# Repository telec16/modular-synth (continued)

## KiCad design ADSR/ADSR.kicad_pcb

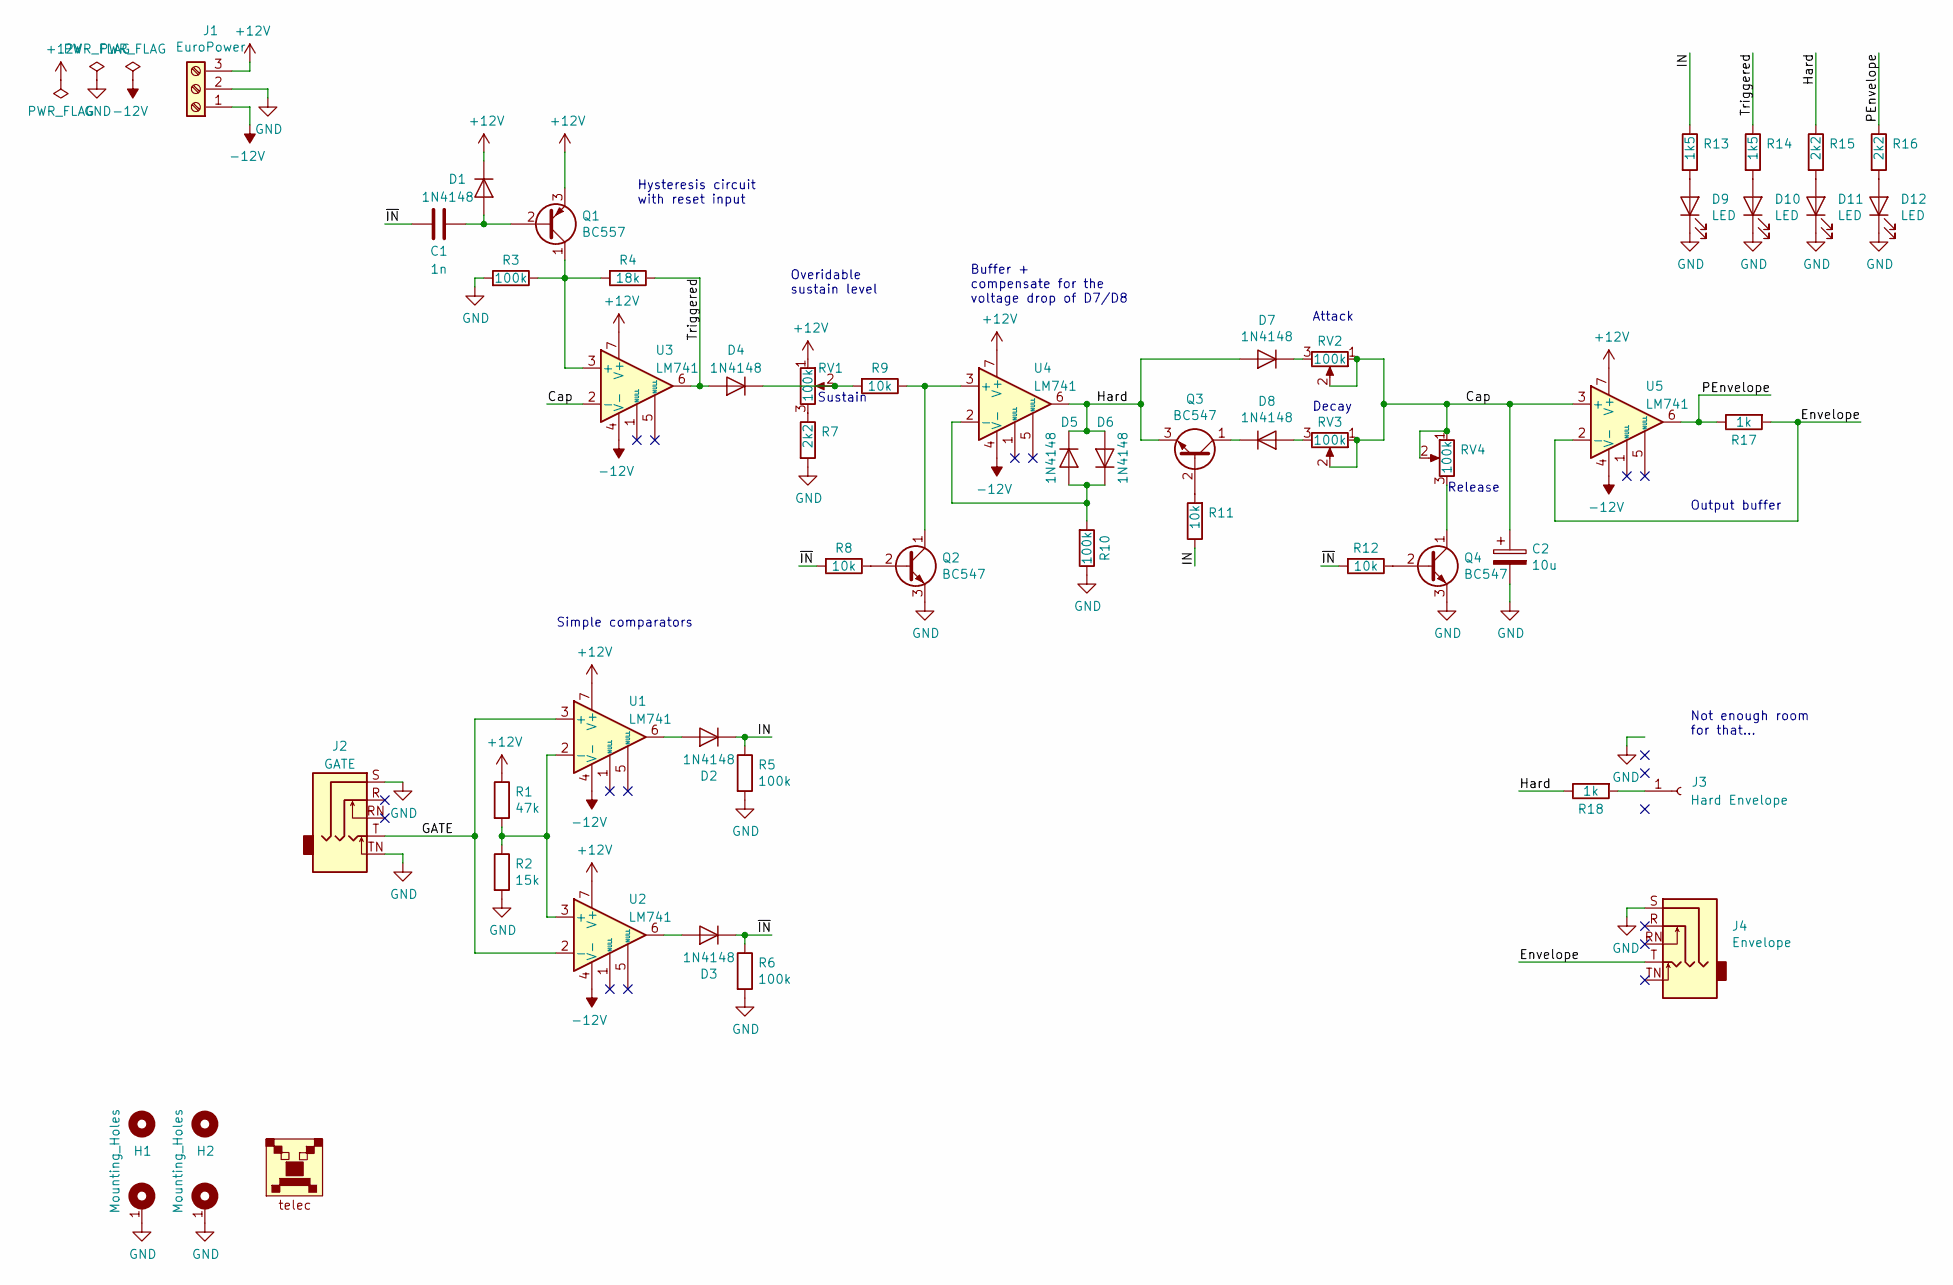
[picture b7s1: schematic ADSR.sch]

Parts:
C1: 1n; C_Disc_D7.0mm_W2.5mm_P5.00mm
C2: 10u; CP_Radial_D6.3mm_P2.50mm
D1, D2, D3, D4, D5, D6, D7, D8: 1N4148; D_DO-35_SOD27_P7.62mm_Horizontal
D9, D10, D11, D12: LED; LED_1206_3216Metric_ReverseMount_Hole1.8x2.4mm
H1, H2: Mounting_Holes; Kosmo_Panel_Dual_Mounting_Holes
J1: EuroPower
J2: GATE; Jack_Hole_Square
J3: Hard Envelope; PinSocket_1x01_P2.54mm_Vertical
J4: Envelope; Jack_Hole_Square
LOGO1: Logo_telec; telec-8
Q1: BC557; TO-92_Inline_Wide
Q2, Q3, Q4: BC547; TO-92_Inline_Wide
R1: 47k; R_Axial_DIN0204_L3.6mm_D1.6mm_P7.62mm_Horizontal
R2: 15k; R_Axial_DIN0204_L3.6mm_D1.6mm_P7.62mm_Horizontal
R3, R5, R6, R10: 100k; R_Axial_DIN0204_L3.6mm_D1.6mm_P7.62mm_Horizontal
R4: 18k; R_Axial_DIN0204_L3.6mm_D1.6mm_P7.62mm_Horizontal
R7: 2k2; R_Axial_DIN0204_L3.6mm_D1.6mm_P7.62mm_Horizontal
R8, R9, R11, R12: 10k; R_Axial_DIN0204_L3.6mm_D1.6mm_P7.62mm_Horizontal
R13, R14: 1k5; R_1206_3216Metric
R15, R16: 2k2; R_1206_3216Metric
R17, R18: 1k; R_Axial_DIN0204_L3.6mm_D1.6mm_P7.62mm_Horizontal
RV1, RV2, RV3, RV4: 100k; Potentiometer_Alps_RK09K_Single_Vertical
U1, U2, U3, U4, U5: LM741; DIP-8_W7.62mm_LongPads

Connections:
+12V: D1.1 (K), J1.3, Q1.3 (E), R1.1, RV1.1, U1.7 (V+), U2.7 (V+), U3.7 (V+), U4.7 (V+), U5.7 (V+)
-12V: J1.1, U1.4 (V-), U2.4 (V-), U3.4 (V-), U4.4 (V-), U5.4 (V-)
/Cap: C2.1, RV2.1, RV2.2, RV3.1, RV3.2, RV4.1, RV4.2, U3.2 (-), U5.3 (+)
/Envelope: J4.T, R17.2, U5.2 (-)
/GATE: J2.T, U1.3 (+), U2.2 (-)
/Hard: D5.1 (K), D6.2 (A), D7.2 (A), Q3.3 (E), R15.1, R18.1, U4.6
/IN: D2.1 (K), R5.1, R11.1, R13.1
/PEnvelope: R16.1, R17.1, U5.6
/Triggered: D4.2 (A), R4.1, R14.1, U3.6
/~IN: C1.2, D3.1 (K), R6.1, R8.2, R12.2
GND: C2.2, D9.1 (K), D10.1 (K), D11.1 (K), D12.1 (K), H1.1, H2.1, J1.2, J2.S, J2.TN, J4.S, Q2.3 (E), Q4.3 (E), R2.2, R3.2, R5.2, R6.2, R7.2, R10.1
unnamed: C1.1, D1.2 (A), Q1.2 (B)
unnamed: D2.2 (A), U1.6
unnamed: D3.2 (A), U2.6
unnamed: D4.1 (K), R9.2, RV1.2
unnamed: D5.2 (A), D6.1 (K), R10.2, U4.2 (-)
unnamed: D7.1 (K), RV2.3
unnamed: D8.1 (K), Q3.1 (C)
unnamed: D8.2 (A), RV3.3
unnamed: D9.2 (A), R13.2
unnamed: D10.2 (A), R14.2
unnamed: D11.2 (A), R15.2
unnamed: D12.2 (A), R16.2
unnamed: J3.1, R18.2
unnamed: Q1.1 (C), R3.1, R4.2, U3.3 (+)
unnamed: Q2.1 (C), R9.1, U4.3 (+)
unnamed: Q2.2 (B), R8.1
unnamed: Q3.2 (B), R11.2
unnamed: Q4.1 (C), RV4.3
unnamed: Q4.2 (B), R12.1
unnamed: R1.2, R2.1, U1.2 (-), U2.3 (+)
unnamed: R7.1, RV1.3

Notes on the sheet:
Attack
Sustain
Decay
Release
Simple comparators
Hysteresis circuit with reset input
Overidable sustain level
Buffer + compensate for the voltage drop of D7/D8
Output buffer
Not enough room for that...

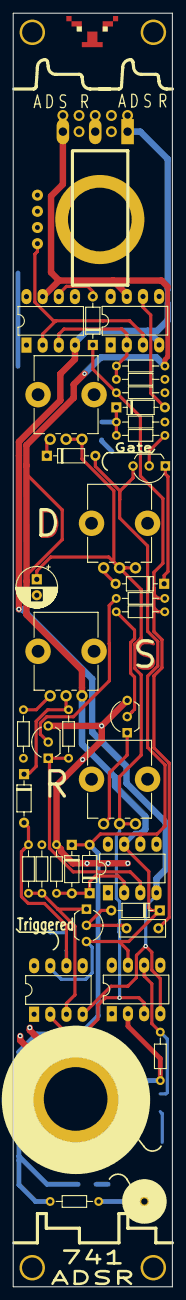
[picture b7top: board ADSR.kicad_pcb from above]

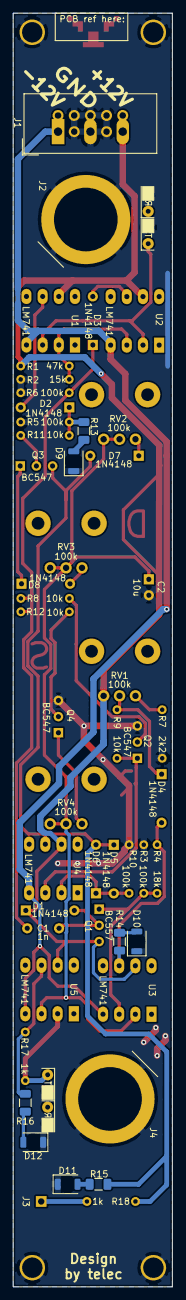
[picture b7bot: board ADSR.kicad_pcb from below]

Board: 2 copper layers, 25.0 x 200.0 mm, 52 parts (9 on the bottom side), 32 nets.

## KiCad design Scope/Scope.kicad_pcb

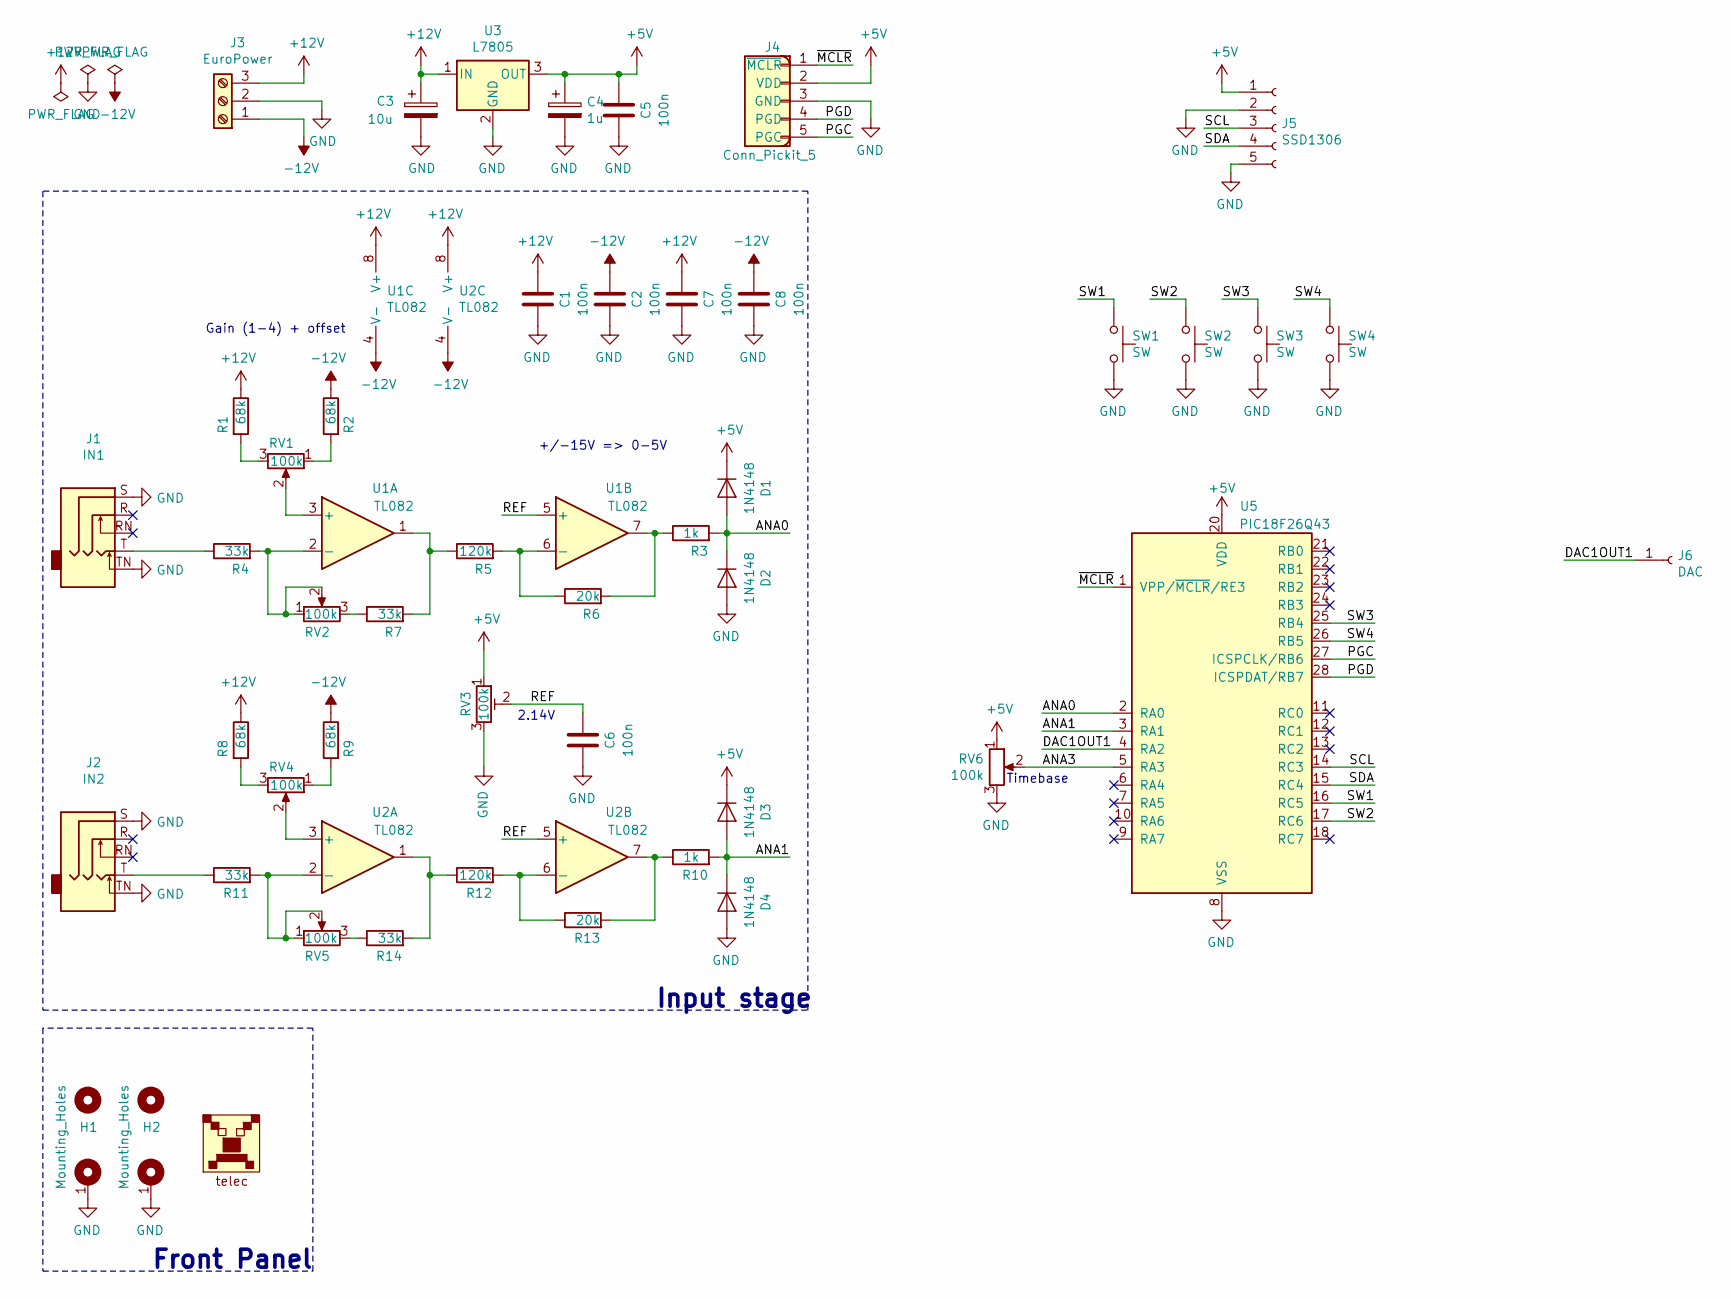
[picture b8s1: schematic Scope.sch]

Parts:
C1, C2, C5, C6, C7, C8: 100n; C_1206_3216Metric_Pad1.42x1.75mm_HandSolder
C3: 10u; CP_Radial_D8.0mm_P3.80mm
C4: 1u; CP_Radial_D8.0mm_P3.80mm
D1, D2, D3, D4: 1N4148; D_1206_3216Metric_Pad1.42x1.75mm_HandSolder
H1, H2: Mounting_Holes; Kosmo_Panel_Dual_Mounting_Holes
J1: IN1; Jack_Hole_Square
J2: IN2; Jack_Hole_Square
J3: EuroPower
J4: Conn_Pickit_5; PinHeader_1x05_P2.54mm_Vertical
J5: SSD1306; SSD1306_096in_I2C
J6: DAC; PinHeader_1x01_P2.54mm_Vertical
LOGO1: telec; telec-8
R1, R2, R8, R9: 68k; R_1206_3216Metric_Pad1.42x1.75mm_HandSolder
R3, R10: 1k; R_1206_3216Metric_Pad1.42x1.75mm_HandSolder
R4, R7, R11, R14: 33k; R_1206_3216Metric_Pad1.42x1.75mm_HandSolder
R5, R12: 120k; R_1206_3216Metric_Pad1.42x1.75mm_HandSolder
R6, R13: 20k; R_1206_3216Metric_Pad1.42x1.75mm_HandSolder
RV1, RV2, RV4, RV5, RV6: 100k; Potentiometer_Single_Vertical_Hole
RV3: 100k; Potentiometer_P3.81mmx5.12mm_Vertical
SW1, SW2, SW3, SW4: SW; SW_PUSH_6mm
U1, U2: TL082; SOIC-8_3.9x4.9mm_P1.27mm
U3: L7805; TO-220-3_Horizontal_TabDown
U5: PIC18F26Q43; SOIC-28W_7.5x17.9mm_P1.27mm

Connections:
+5V: C4.1, C5.2, D1.1 (K), D3.1 (K), J4.2 (VDD), J5.1, RV3.1, RV6.1, U3.3 (OUT), U5.20 (VDD)
+12V: C1.2, C3.1, C7.2, J3.3, R1.1, R8.1, U1.8 (V+), U2.8 (V+), U3.1 (IN)
-12V: C2.2, C8.2, J3.1, R2.1, R9.1, U1.4 (V-), U2.4 (V-)
/ANA0: D1.2 (A), D2.1 (K), R3.2, U5.2 (RA0)
/ANA1: D3.2 (A), D4.1 (K), R10.2, U5.3 (RA1)
/ANA3: RV6.2, U5.5 (RA3)
/DAC1OUT1: J6.1, U5.4 (RA2)
/PGC: J4.5 (PGC), U5.27 (ICSPCLK/RB6)
/PGD: J4.4 (PGD), U5.28 (ICSPDAT/RB7)
/REF: C6.2, RV3.2, U1.5 (+), U2.5 (+)
/SCL: J5.3, U5.14 (RC3)
/SDA: J5.4, U5.15 (RC4)
/SW1: SW1.1, U5.16 (RC5)
/SW2: SW2.1, U5.17 (RC6)
/SW3: SW3.1, U5.25 (RB4)
/SW4: SW4.1, U5.26 (RB5)
/~MCLR: J4.1 (~MCLR), U5.1 (VPP/~MCLR~/RE3)
GND: C1.1, C2.1, C3.2, C4.2, C5.1, C6.1, C7.1, C8.1, D2.2 (A), D4.2 (A), H1.1, H2.1, J1.S, J1.TN, J2.S, J2.TN, J3.2, J4.3 (GND), J5.2, J5.5, RV3.3, RV6.3, SW1.2, SW2.2, SW3.2, SW4.2, U3.2 (GND), U5.8 (VSS), U5.19 (VSS)
unnamed: J1.T, R4.1
unnamed: J2.T, R11.1
unnamed: R1.2, RV1.3
unnamed: R2.2, RV1.1
unnamed: R3.1, R6.2, U1.7
unnamed: R4.2, RV2.1, RV2.2, U1.2 (-)
unnamed: R5.1, R7.2, U1.1
unnamed: R5.2, R6.1, U1.6 (-)
unnamed: R7.1, RV2.3
unnamed: R8.2, RV4.3
unnamed: R9.2, RV4.1
unnamed: R10.1, R13.2, U2.7
unnamed: R11.2, RV5.1, RV5.2, U2.2 (-)
unnamed: R12.1, R14.2, U2.1
unnamed: R12.2, R13.1, U2.6 (-)
unnamed: R14.1, RV5.3
unnamed: RV1.2, U1.3 (+)
unnamed: RV4.2, U2.3 (+)

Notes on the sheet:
Front Panel
Timebase
2.14V
Input stage
+/-15V => 0-5V
Gain (1-4) + offset

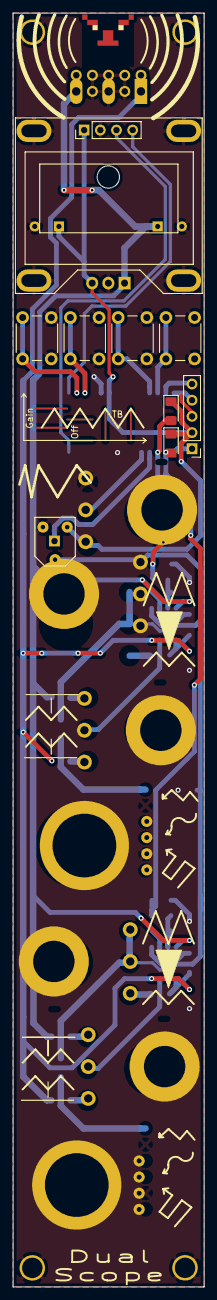
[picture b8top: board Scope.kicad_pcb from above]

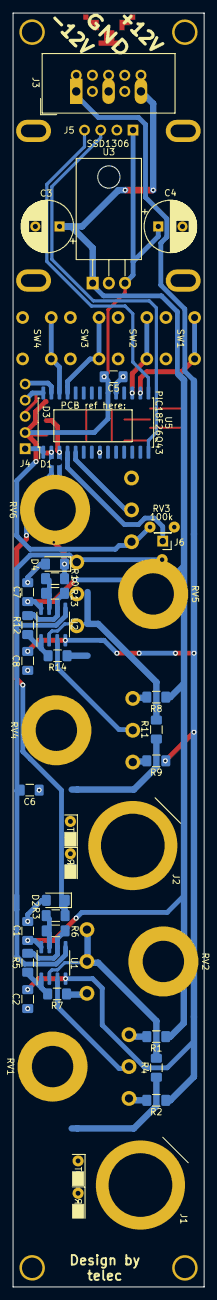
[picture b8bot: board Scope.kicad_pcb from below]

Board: 2 copper layers, 30.0 x 200.0 mm, 49 parts (30 on the bottom side), 36 nets.

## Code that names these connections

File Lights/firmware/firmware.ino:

#define IN1 A2  //PC2
#define IN2 A1  //PC1
#define IN3 A0  //PC0
#define OUT1 9  //PB1
#define OUT2 10 //PB2
#define OUT3 3  //PD3
#define SW3 7   //PD7
#define SW2 6   //PD6
#define SW1 5   //PD5
#define SW0 4   //PD4
#define INOUTS 3

const byte IN[INOUTS] = {IN1, IN2, IN3};
const byte OUT[INOUTS] = {OUT1, OUT2, OUT3};
volatile byte jacks[INOUTS] = {0};

void setup(){
  pinMode(OUT1, OUTPUT);
  pinMode(OUT2, OUTPUT);
  pinMode(OUT3, OUTPUT);
  pinMode(SW0, INPUT_PULLUP);
  pinMode(SW1, INPUT_PULLUP);
  pinMode(SW2, INPUT_PULLUP);
  pinMode(SW3, INPUT_PULLUP);

  Serial.begin(31250);
}

void loop() {
  readJacks();
  writeLights();

  if(digitalRead(SW3))
    sendStates();

  delay(100);
}

void readJacks(){
  for(byte i=0; i<INOUTS; i++){
    jacks[i] = analogRead(IN[i])>>2;
    delay(1);
  }
}

void writeLights(){
  for(byte i=0; i<INOUTS; i++){
    analogWrite(OUT[i], jacks[i]);
  }
}

void sendStates(){
  for(byte i=0; i<INOUTS; i++){
    sendMIDI(i, jacks[i]);
  }
}

void sendMIDI(byte cmd, byte data){
  Serial.print(cmd);
  Serial.print(data);
}

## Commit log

2020-05-18 ADSR test file - OK
2020-07-12 VCO, to be tested IRL
2020-07-12 Ramp, not good
2020-07-12 R2T, works great, to be tested IRL
2020-07-12 S2R, need AGC...
2020-07-12 ADSR layout, can't fit on 100mm board
2020-07-13 could fit with 200mm
2020-07-24 List of what I want
2020-07-24 Wave folder sim files
2020-07-24 VCO PCB
2020-08-10 New project! Needs test and layout
2020-08-11 Small improvements
2020-08-11 Schematic done
2020-08-11 First layout fit
2020-08-11 Layout improvment
2020-08-11 Layout only needs the finishing touches!
2020-08-11 Well it's better with the actual layout file...
2020-08-11 Finsihed layout
2020-08-11 PCB art!
2020-08-12 Corrected error
2020-08-12 Cleaner schematic, Better Layout
2020-08-12 Finished graphics
2020-08-12 References and values correctly positionned
2020-08-12 Minor tweaks; added BOM
2020-08-12 Added schematic
2020-08-12 Look! I made a stickman!
2020-08-13 Small tweak
2020-08-13 VCA - finished, needs review
2020-08-13 Will it fits ?
2020-08-13 Glider !
2020-08-14 Glider done !
2020-08-14 VCA done !
2020-08-14 It fits !
2020-08-14 Now the power lines...
2020-08-14 Layout done! Art to do
2020-08-15 ADSR done !
2020-08-15 Changed pot direction
2020-08-15 PLL project
2020-08-15 VCO - Nice schematic
2020-08-15 VCO layout done!
2020-08-15 Starting the PLL
2020-08-16 Created scope project
2020-08-16 PLL layout done
2020-08-16 File restructuration
2020-08-16 Progress bar!
2020-08-16 Scope schematic done, how I will fit that?
2020-08-16 PLL done !
2020-08-16 VCO done !
2020-08-16 RJG done !
2020-08-16 MiniSynth, not sure about it...
2020-08-16 Quantizer...
2020-08-17 Quantizer layout done!
2020-08-17 Quantizer done!
2020-08-17 Wavefolder, will it fits ?
2020-08-17 Typo
2020-08-18 Wavefolder layout
2020-08-18 Wavefolder design
2020-08-18 fixing folder case...
2020-08-18 Scope layout
2020-08-18 Scope done !
2020-08-18 Wavefolder done !
2020-08-18 Added PCB ref stamp and send to prod!
2020-08-22 fix badly connected pin
2020-08-22 new module!
2020-08-23 Drum modules!
2020-08-23 fix naming
2020-08-30 808 bass drum
2020-08-30 fix RJG
2020-08-30 JFET VCA
2020-09-07 Wavefolder done and tested!
2020-09-07 VCA done and tested!
2020-09-07 Analog modules finished
2020-09-11 fix stuffs
2020-09-11 Refactor VCO
2020-09-12 New PCB
2020-09-12 Layout VCO
2020-09-12 Layout VCO done
2020-09-13 VCO artwork done
2020-09-13 updated footprints on ADSR
2020-09-13 updated footprints on Glider
2020-09-13 updated footprints on Wavefolder
2020-09-13 updated footprints on VCA
2020-09-13 updated footprints on Quantizer
2020-09-13 updated footprints on Scope, not done...
2020-09-13 Started PLL layout
2020-09-13 VCO done
2020-09-13 PLL done
2020-09-13 Prepared for release
2021-01-30 Added HF trim, ready to fab
2021-01-30 ADSR ready for prod
2021-01-30 VCA ready for prod
2021-01-31 More clearance
2021-02-03 Light control
2021-02-07 Finished schematic and routing
2021-02-07 Finished artwork
2021-02-08 Split PCB
2022-10-31 Small fixes+firmware
2023-07-25 Switched to kicad 7 + small fixes
